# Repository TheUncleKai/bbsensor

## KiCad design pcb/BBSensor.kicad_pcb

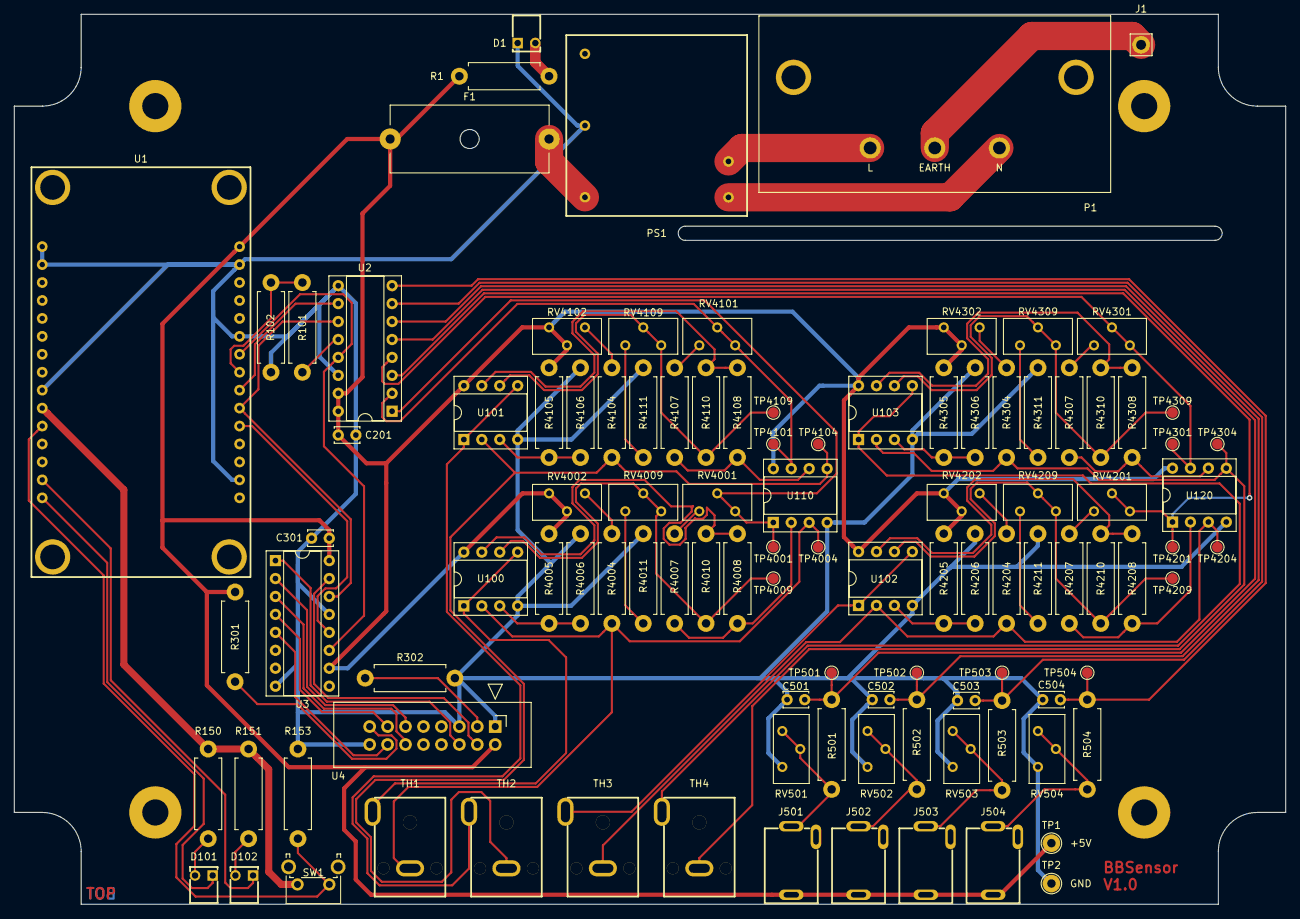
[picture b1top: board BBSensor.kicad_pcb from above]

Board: 2 copper layers, 180.0 x 126.0 mm, 106 parts (0 on the bottom side), 75 nets.

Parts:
C201, C301, C501, C502, C503, C504: 100n; C_Disc_D3.4mm_W2.1mm_P2.50mm
D1: POWER; 5600F
D101: RED; 5600F
D102: GREEN; 5600F
F1: Fuse; Fuse_holder_20x5_22.5
J1: Earth; Terminal_Pin_D1.3_L10.0_PL4.0
J501, J502, J503, J504: AudioJack2_SwitchT; LUMBERG_1501_09
P1: Conn_WallPlug_Earth; PX0580PC
PS1: TMPS_05; Traco_TMPS_05
R1, R301: 220; R_Axial_DIN0411_L9.9mm_D3.6mm_P12.70mm_Horizontal
R101: 1k; R_Axial_DIN0411_L9.9mm_D3.6mm_P12.70mm_Horizontal
R102, R153, R4004, R4104, R4204, R4304: 2k2; R_Axial_DIN0411_L9.9mm_D3.6mm_P12.70mm_Horizontal
R150, R151: 140; R_Axial_DIN0411_L9.9mm_D3.6mm_P12.70mm_Horizontal
R302, R4011, R4111, R4211, R4311: 2k; R_Axial_DIN0411_L9.9mm_D3.6mm_P12.70mm_Horizontal
R501, R502, R503, R504, R4005, R4006, R4105, R4106, R4205, R4206, R4305, R4306: 10k; R_Axial_DIN0411_L9.9mm_D3.6mm_P12.70mm_Horizontal
R4007, R4107, R4207, R4307: 4k7; R_Axial_DIN0411_L9.9mm_D3.6mm_P12.70mm_Horizontal
R4008, R4010, R4108, R4110, R4208, R4210, R4308, R4310: 200; R_Axial_DIN0411_L9.9mm_D3.6mm_P12.70mm_Horizontal
RV501, RV502, RV503, RV504: 10k; Potentiometer_Bourns_3296Y_Vertical
RV4001, RV4101, RV4201, RV4301: 405; Potentiometer_Bourns_3296Y_Vertical
RV4002, RV4102, RV4202, RV4302: 300; Potentiometer_Bourns_3296Y_Vertical
RV4009, RV4109, RV4209, RV4309: 470; Potentiometer_Bourns_3296Y_Vertical
SW1: SW_Push; SW_Tactile_SPST_Angled_PTS645Vx83-2LFS
TH1, TH2, TH3, TH4: Thermistor_NTC; LUMBERG_1553_02
TP1, TP2: TestPoint; TestPoint_THTPad_D2.5mm_Drill1.2mm
TP501, TP502, TP503, TP504, TP4001, TP4004, TP4009, TP4101, TP4104, TP4109, TP4201, TP4204, TP4209, TP4301, TP4304, TP4309: TestPoint; TestPoint_Pad_D1.5mm
U1: ESP8266-12E_NodeMCU_Lolin
U2: MCP3208; DIP-16_W7.62mm_Socket
U3: 74HC595; DIP-16_W7.62mm_Socket
U4: HD44780; Box_Header_Straight_2x08
U100, U101, U102, U103, U110, U120: OPA2340; DIP-8_W7.62mm_Socket

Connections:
+3V3: R150.1, R151.1, SW1.2, U1.21
+5V: C201.1, C301.1, F1.1, J501.S, J502.S, J503.S, J504.S, R1.2, R301.1, R4005.2, R4105.2, R4205.2, R4305.2, RV4002.2, RV4002.3, RV4102.2, RV4102.3, RV4202.2, RV4202.3, RV4302.2, RV4302.3, TP1.1, U1.15, U2.15, U2.16, U3.10, U3.16, U4.2, U100.8, U101.8, U102.8, U103.8, U110.8, U120.8
/Analog/Digital/SPI1: U1.6, U2.11, U3.14
/Analog/Digital/SPI2: R101.2, U2.12
/Analog/Digital/SPI3: U1.9, U2.13, U3.11
/Analog/Digital/SPI4: U1.7, U2.10
/Analog/Digital/TEMP1: RV4001.2, RV4001.3, TP4001.1, U2.1, U110.1
/Analog/Digital/TEMP2: RV4101.2, RV4101.3, TP4101.1, U2.2, U110.7
/Analog/Digital/TEMP3: RV4201.2, RV4201.3, TP4201.1, U2.3, U120.1
/Analog/Digital/TEMP4: RV4301.2, RV4301.3, TP4301.1, U2.4, U120.7
/Analog/Digital/TEMP5: C501.1, R501.1, TP501.1, U2.5
/Analog/Digital/TEMP6: C502.1, R502.1, TP502.1, U2.6
/Analog/Digital/TEMP7: C503.1, R503.1, TP503.1, U2.7
/Analog/Digital/TEMP8: C504.1, R504.1, TP504.1, U2.8
/Display/DB4: U3.2, U4.11
/Display/DB5: U3.3, U4.12
/Display/DB6: U3.4, U4.13
/Display/DB7: U3.5, U4.14
/Display/ENABLE: U3.1, U4.6
/Display/RS: U3.15, U4.4
/Display/SPI5: U1.5, U3.12
/ESP8266/MISO: R101.1, R102.1, U1.8
GND: C201.2, C301.2, C501.2, C502.2, C503.2, C504.2, D1.1, PS1.4, R102.2, R153.2, R302.2, R4006.1, R4011.2, R4106.1, R4111.2, R4206.1, R4211.2, R4306.1, R4311.2, RV501.3, RV502.3, RV503.3, RV504.3, TP2.1, U1.2, U1.10, U1.14, U1.22, U1.29, U1.30, U2.9, U2.14, U3.8, U3.13, U4.1, U4.5, U4.16, U100.4, U101.4, U102.4, U103.4, U110.4, U120.4
unnamed: D1.2, R1.1
unnamed: D101.1, U1.16
unnamed: D101.2, R150.2
unnamed: D102.1, U1.17
unnamed: D102.2, R151.2
unnamed: F1.2, PS1.5
unnamed: J1.1, P1.3
unnamed: J501.T, R501.2, RV501.1, RV501.2
unnamed: J502.T, R502.2, RV502.1, RV502.2
unnamed: J503.T, R503.2, RV503.1, RV503.2
unnamed: J504.T, R504.2, RV504.1, RV504.2
unnamed: P1.1, PS1.2
unnamed: P1.2, PS1.1
unnamed: R153.1, SW1.1, U1.20
unnamed: R301.2, U4.15
unnamed: R302.1, U4.3
unnamed: R4004.1, TH1.2, TP4004.1, U100.2, U110.3
unnamed: R4004.2, RV4002.1
unnamed: R4005.1, R4006.2, U100.3
unnamed: R4007.1, RV4001.1
unnamed: R4007.2, R4008.1, U110.2
unnamed: R4008.2, R4010.1, U100.7
unnamed: R4010.2, RV4009.2, RV4009.3, TP4009.1, U100.6
unnamed: R4011.1, RV4009.1
unnamed: R4104.1, TH2.2, TP4104.1, U101.2, U110.5
unnamed: R4104.2, RV4102.1
unnamed: R4105.1, R4106.2, U101.3
unnamed: R4107.1, RV4101.1
unnamed: R4107.2, R4108.1, U110.6
unnamed: R4108.2, R4110.1, U101.7
unnamed: R4110.2, RV4109.2, RV4109.3, TP4109.1, U101.6
unnamed: R4111.1, RV4109.1
unnamed: R4204.1, TH3.2, TP4204.1, U102.2, U120.3
unnamed: R4204.2, RV4202.1
unnamed: R4205.1, R4206.2, U102.3
unnamed: R4207.1, RV4201.1
unnamed: R4207.2, R4208.1, U120.2
unnamed: R4208.2, R4210.1, U102.7
unnamed: R4210.2, RV4209.2, RV4209.3, TP4209.1, U102.6
unnamed: R4211.1, RV4209.1
unnamed: R4304.1, TH4.2, TP4304.1, U103.2, U120.5
unnamed: R4304.2, RV4302.1
unnamed: R4305.1, R4306.2, U103.3
unnamed: R4307.1, RV4301.1
unnamed: R4307.2, R4308.1, U120.6
unnamed: R4308.2, R4310.1, U103.7
unnamed: R4310.2, RV4309.2, RV4309.3, TP4309.1, U103.6
unnamed: R4311.1, RV4309.1
unnamed: TH1.1, U100.1, U100.5
unnamed: TH2.1, U101.1, U101.5
unnamed: TH3.1, U102.1, U102.5
unnamed: TH4.1, U103.1, U103.5
